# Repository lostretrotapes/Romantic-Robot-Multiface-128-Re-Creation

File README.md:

# Romantic-Robot-Multiface-128-Re-Creation

This is a copy of the recreation that used to be hosted at http://projectspeccy.com/projects/ with permission from Steve Smith

https://www.lostretrotapes.com/romantic-robot-multiface-128-re-creation/

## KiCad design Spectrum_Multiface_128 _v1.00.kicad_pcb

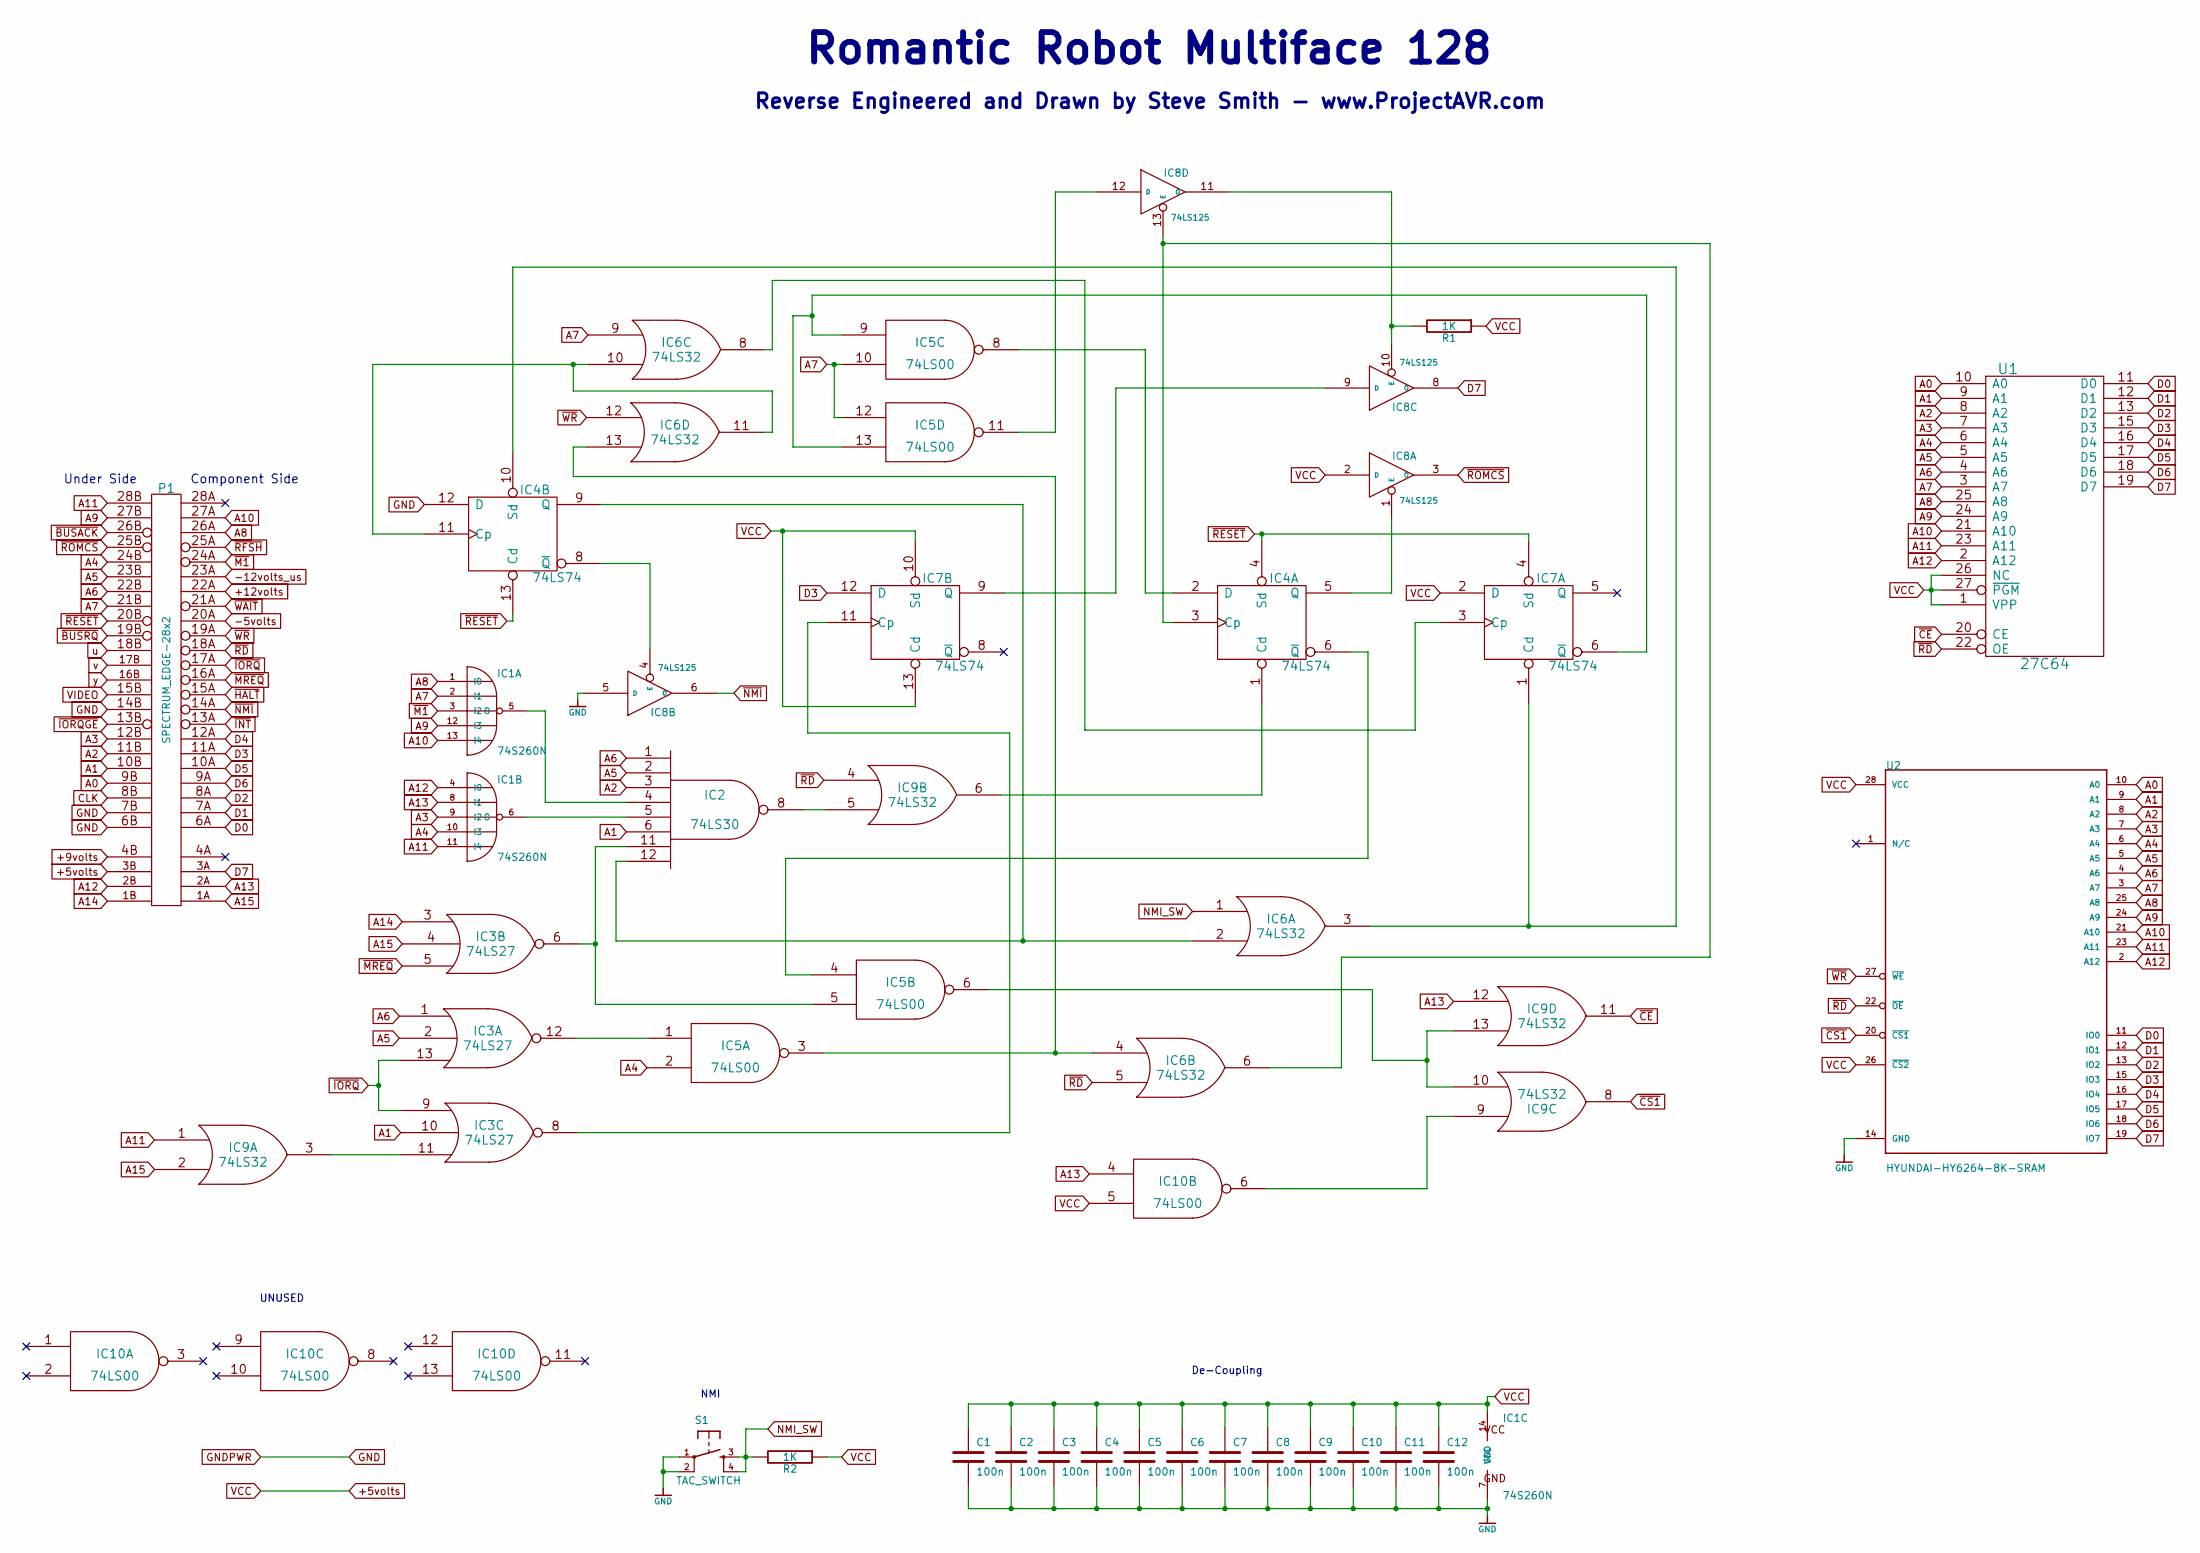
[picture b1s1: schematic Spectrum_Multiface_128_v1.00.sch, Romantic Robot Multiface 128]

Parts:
C1, C2, C3, C4, C5, C6, C7, C8, C9, C10, C11, C12: 100n; C_Disc_D3.4mm_W2.1mm_P2.50mm
IC1: 74S260N; DIP-14_W7.62mm
IC2: 74LS30; DIP-14_W7.62mm
IC3: 74LS27; DIP-14_W7.62mm
IC4, IC7: 74LS74; DIP-14_W7.62mm
IC5, IC10: 74LS00; DIP-14_W7.62mm
IC6, IC9: 74LS32; DIP-14_W7.62mm
IC8: 74LS125; DIP-14_W7.62mm
P1: SPECTRUM_EDGE-28x2; Spectrum_Edge_Connector
R1, R2: 1K; R_Axial_DIN0207_L6.3mm_D2.5mm_P10.16mm_Horizontal
S1: TAC_SWITCH; TACTILE-PTH
U1: 27C64; DIP-28_W15.24mm
U2: HYUNDAI-HY6264-8K-SRAM; DIP-28_W15.24mm

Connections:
+5volts: C1.1, C2.1, C3.1, C4.1, C5.1, C6.1, C7.1, C8.1, C9.1, C10.1, C11.1, C12.1, IC1.14 (VCC), IC2.14 (VCC), IC3.14 (VCC), IC4.14 (VCC), IC5.14 (VCC), IC6.14 (VCC), IC7.2 (D), IC7.10 (Sd), IC7.13 (Cd), IC7.14 (VCC), IC8.2 (D), IC8.14 (VCC), IC9.14 (VCC), IC10.5, IC10.14 (VCC), P1.3B (+5volts), R1.1, R2.1, U1.1 (VPP), U1.26 (NC), U1.27 (~PGM), U1.28 (VCC), U2.26 (~CS2), U2.28 (VCC)
+9volts: P1.4B (+9volts)
+12volts: P1.22A (+12volts)
-5volts: P1.20A (-5volts)
-12volts_us: P1.23A (+12volts_unsmoothed)
A0: P1.9B (A0), U1.10 (A0), U2.10 (A0)
A1: IC2.6, IC3.10, P1.10B (A1), U1.9 (A1), U2.9 (A1)
A2: IC2.3, P1.11B (A2), U1.8 (A2), U2.8 (A2)
A3: IC1.9 (I2), P1.12B (A3), U1.7 (A3), U2.7 (A3)
A4: IC1.10 (I3), IC5.2, P1.24B (A4), U1.6 (A4), U2.6 (A4)
A5: IC2.2, IC3.2, P1.23B (A5), U1.5 (A5), U2.5 (A5)
A6: IC2.1, IC3.1, P1.22B (A6), U1.4 (A6), U2.4 (A6)
A7: IC1.2 (I1), IC5.10, IC5.12, IC6.9, P1.21B (A7), U1.3 (A7), U2.3 (A7)
A8: IC1.1 (I0), P1.26A (A8), U1.25 (A8), U2.25 (A8)
A9: IC1.12 (I3), P1.27B (A9), U1.24 (A9), U2.24 (A9)
A10: IC1.13 (I4), P1.27A (A10), U1.21 (A10), U2.21 (A10)
A11: IC1.11 (I4), IC9.1, P1.28B (A11), U1.23 (A11), U2.23 (A11)
A12: IC1.4 (I0), P1.2B (A12), U1.2 (A12), U2.2 (A12)
A13: IC1.8 (I1), IC9.12, IC10.4, P1.2A (A13)
A14: IC3.3, P1.1B (A14)
A15: IC3.4, IC9.2, P1.1A (A15)
CLK: P1.8B (CLK)
D0: P1.6A (D0), U1.11 (D0), U2.11 (IO0)
D1: P1.7A (D1), U1.12 (D1), U2.12 (IO1)
D2: P1.8A (D2), U1.13 (D2), U2.13 (IO2)
D3: IC7.12 (D), P1.11A (D3), U1.15 (D3), U2.15 (IO3)
D4: P1.12A (D4), U1.16 (D4), U2.16 (IO4)
D5: P1.10A (D5), U1.17 (D5), U2.17 (IO5)
D6: P1.9A (D6), U1.18 (D6), U2.18 (IO6)
D7: IC8.8 (O), P1.3A (D7), U1.19 (D7), U2.19 (IO7)
GND: C1.2, C2.2, C3.2, C4.2, C5.2, C6.2, C7.2, C8.2, C9.2, C10.2, C11.2, C12.2, IC1.7 (GND), IC2.7 (GND), IC3.7 (GND), IC4.7 (GND), IC4.12 (D), IC5.7 (GND), IC6.7 (GND), IC7.7 (GND), IC8.5 (D), IC8.7 (GND), IC9.7 (GND), IC10.7 (GND), P1.6B (GND), P1.7B (GND), P1.14B (GND), S1.1, S1.2, U1.14 (GND), U2.14 (GND)
NMI_SW: IC6.1, R2.2, S1.3, S1.4
unnamed: IC1.5 (O), IC2.4
unnamed: IC1.6 (O), IC2.5
unnamed: IC2.8, IC9.5
unnamed: IC2.11, IC3.6, IC5.5
unnamed: IC2.12, IC4.9 (Q), IC6.2
unnamed: IC3.8, IC7.11 (Cp)
unnamed: IC3.11, IC9.3
unnamed: IC3.12, IC5.1
unnamed: IC4.1 (Cd), IC9.6
unnamed: IC4.2 (D), IC5.8
unnamed: IC4.3 (Cp), IC6.6, IC8.13 (E)
unnamed: IC4.5 (Q), IC8.1 (E)
unnamed: IC4.6 (~Q), IC5.4
unnamed: IC4.8 (~Q), IC8.4 (E)
unnamed: IC4.10 (Sd), IC6.3, IC7.1 (Cd)
unnamed: IC4.11 (Cp), IC6.10, IC6.11
unnamed: IC5.3, IC6.4, IC6.13
unnamed: IC5.6, IC9.10, IC9.13
unnamed: IC5.11, IC8.12 (D)
unnamed: IC5.9, IC5.13, IC7.6 (~Q)
unnamed: IC6.8, IC7.3 (Cp)
unnamed: IC7.9 (Q), IC8.9 (D)
unnamed: IC8.10 (E), IC8.11 (O), R1.2
unnamed: IC9.9, IC10.6
VIDEO: P1.15B (VIDEO)
u: P1.18B (u)
v: P1.17B (v)
y: P1.16B (y)
~BUSACK: P1.26B (~BUSACK)
~BUSRQ: P1.19B (~BUSRQ)
~CE: IC9.11, U1.20 (CE)
~CS1: IC9.8, U2.20 (~CS1)
~HALT: P1.15A (~HALT)
~INT: P1.13A (!INT)
~IORQ: IC3.9, IC3.13, P1.17A (~IORQ)
~IORQGE: P1.13B (~IORQGE)
~M1: IC1.3 (I2), P1.24A (~M1)
~MREQ: IC3.5, P1.16A (~MREQ)
~NMI: IC8.6 (O), P1.14A (~NMI)
~RD: IC6.5, IC9.4, P1.18A (~RD), U1.22 (OE), U2.22 (~OE)
~RESET: IC4.4 (Sd), IC4.13 (Cd), IC7.4 (Sd), P1.20B (~RESET)
~RFSH: P1.25A (~RFSH)
~ROMCS: IC8.3 (O), P1.25B (~ROMCS)
~WAIT: P1.21A (~WAIT)
~WR: IC6.12, P1.19A (~WR), U2.27 (~WE)

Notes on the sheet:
Component Side
Under Side
NMI
Romantic Robot Multiface 128
Reverse Engineered and Drawn by Steve Smith - www.ProjectAVR.com
UNUSED
De-Coupling

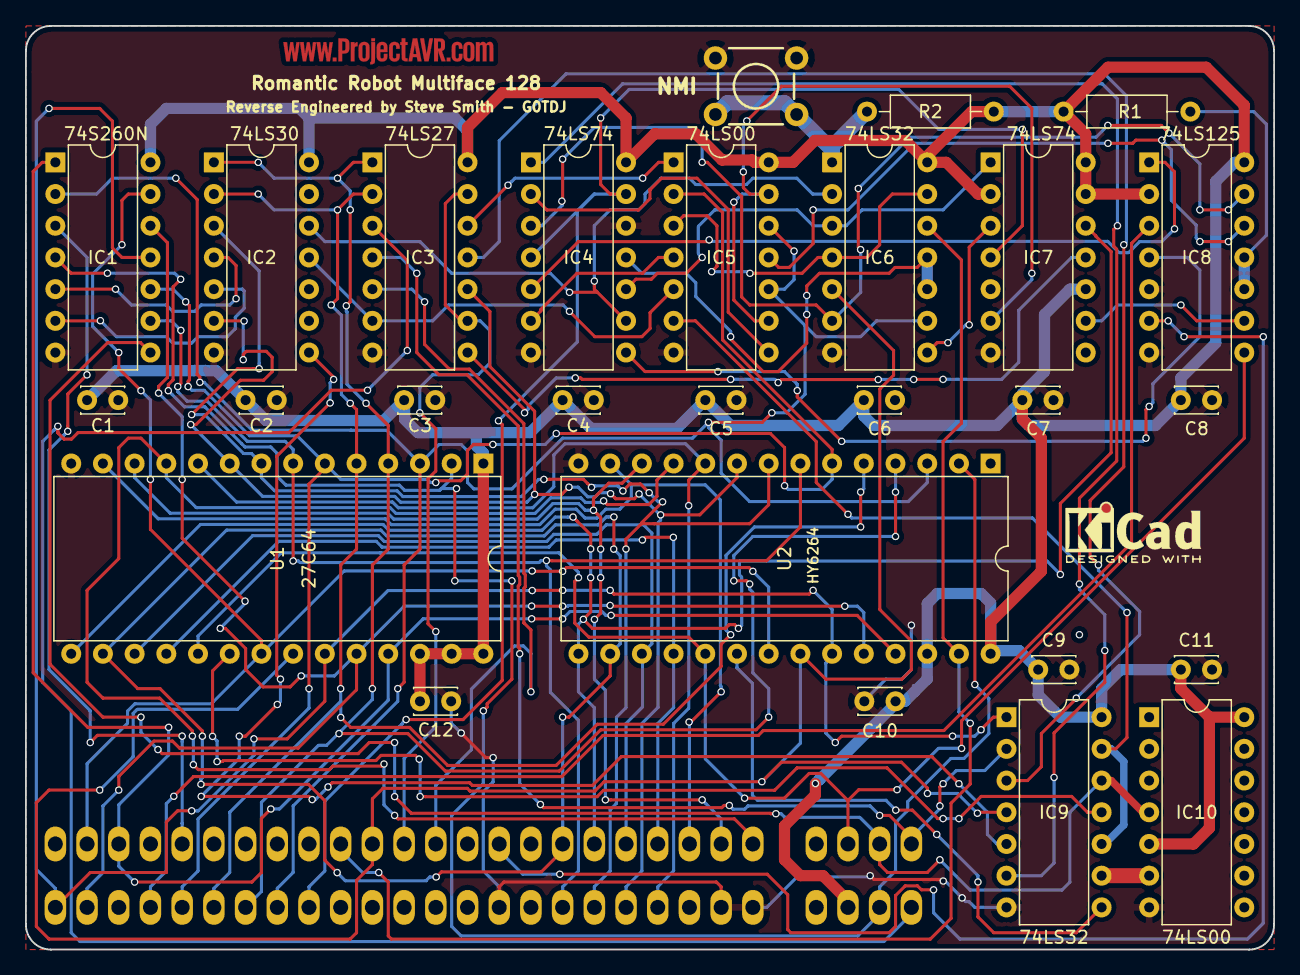
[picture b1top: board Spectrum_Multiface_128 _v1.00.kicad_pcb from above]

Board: 2 copper layers, 100.0 x 74.0 mm, 28 parts (1 on the bottom side), 61 nets.
